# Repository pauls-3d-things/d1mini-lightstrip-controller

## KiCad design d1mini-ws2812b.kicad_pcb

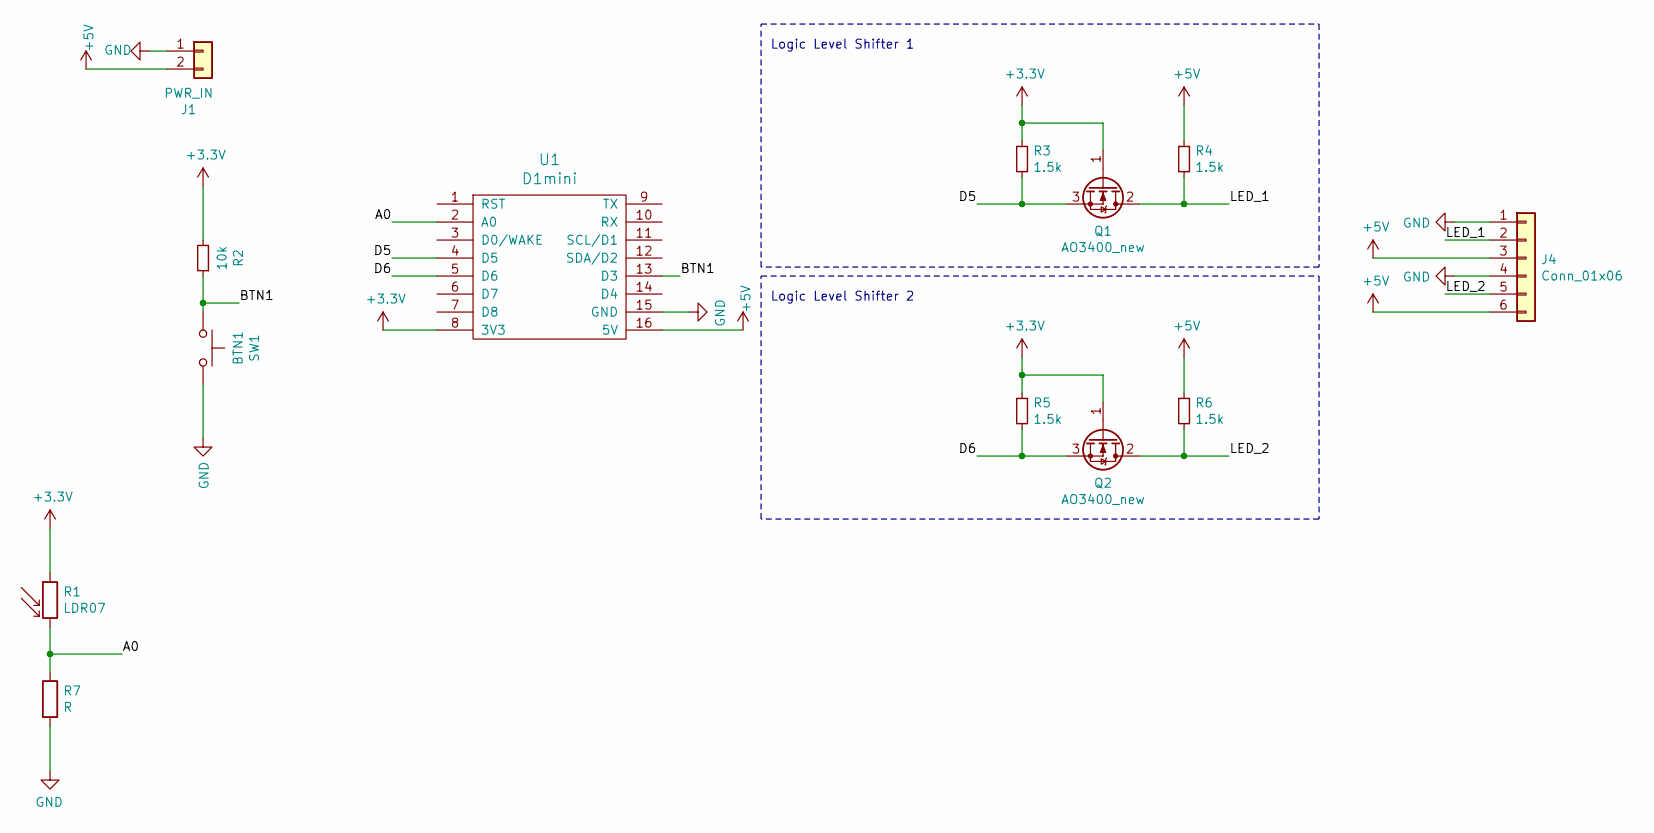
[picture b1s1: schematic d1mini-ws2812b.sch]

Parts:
J1: PWR_IN; TerminalBlock_Phoenix_PT-1,5-2-5.0-H_1x02_P5.00mm_Horizontal
J4: Conn_01x06; TerminalBlock_Phoenix_PT-1,5-6-5.0-H_1x06_P5.00mm_Horizontal
Q1, Q2: AO3400_new; AO340X
R1: LDR07; R_LDR_5.1x4.3mm_P3.4mm_Vertical
R2: 10k; R_0603_1608Metric_Pad1.05x0.95mm_HandSolder
R3, R4, R5, R6: 1.5k; R_0603_1608Metric_Pad1.05x0.95mm_HandSolder
R7: R; R_0603_1608Metric_Pad1.05x0.95mm_HandSolder
SW1: BTN1; SW_PUSH_6mm
U1: D1mini

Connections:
+3V3: Q1.1 (G), Q2.1 (G), R1.1, R2.2, R3.1, R5.1, U1.8 (3V3)
+5V: J1.2, J4.3, J4.6, R4.1, R6.1, U1.16 (5V)
/A0: R1.2, R7.1, U1.2 (A0)
/BTN1: R2.1, SW1.1, U1.13 (D3)
/D5: Q1.3 (S), R3.2, U1.4 (D5)
/D6: Q2.3 (S), R5.2, U1.5 (D6)
/LED_1: J4.2, Q1.2 (D), R4.2
/LED_2: J4.5, Q2.2 (D), R6.2
GND: J1.1, J4.1, J4.4, R7.2, SW1.2, U1.15 (GND)

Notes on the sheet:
Logic Level Shifter 1
Logic Level Shifter 2

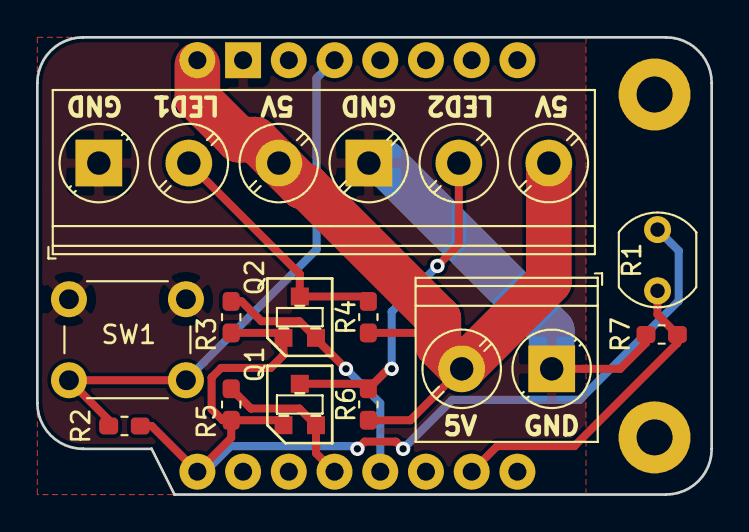
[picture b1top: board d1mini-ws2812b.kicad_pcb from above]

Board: 2 copper layers, 37.5 x 25.4 mm, 13 parts (1 on the bottom side), 9 nets.

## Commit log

2020-01-05 remove copy paste error
